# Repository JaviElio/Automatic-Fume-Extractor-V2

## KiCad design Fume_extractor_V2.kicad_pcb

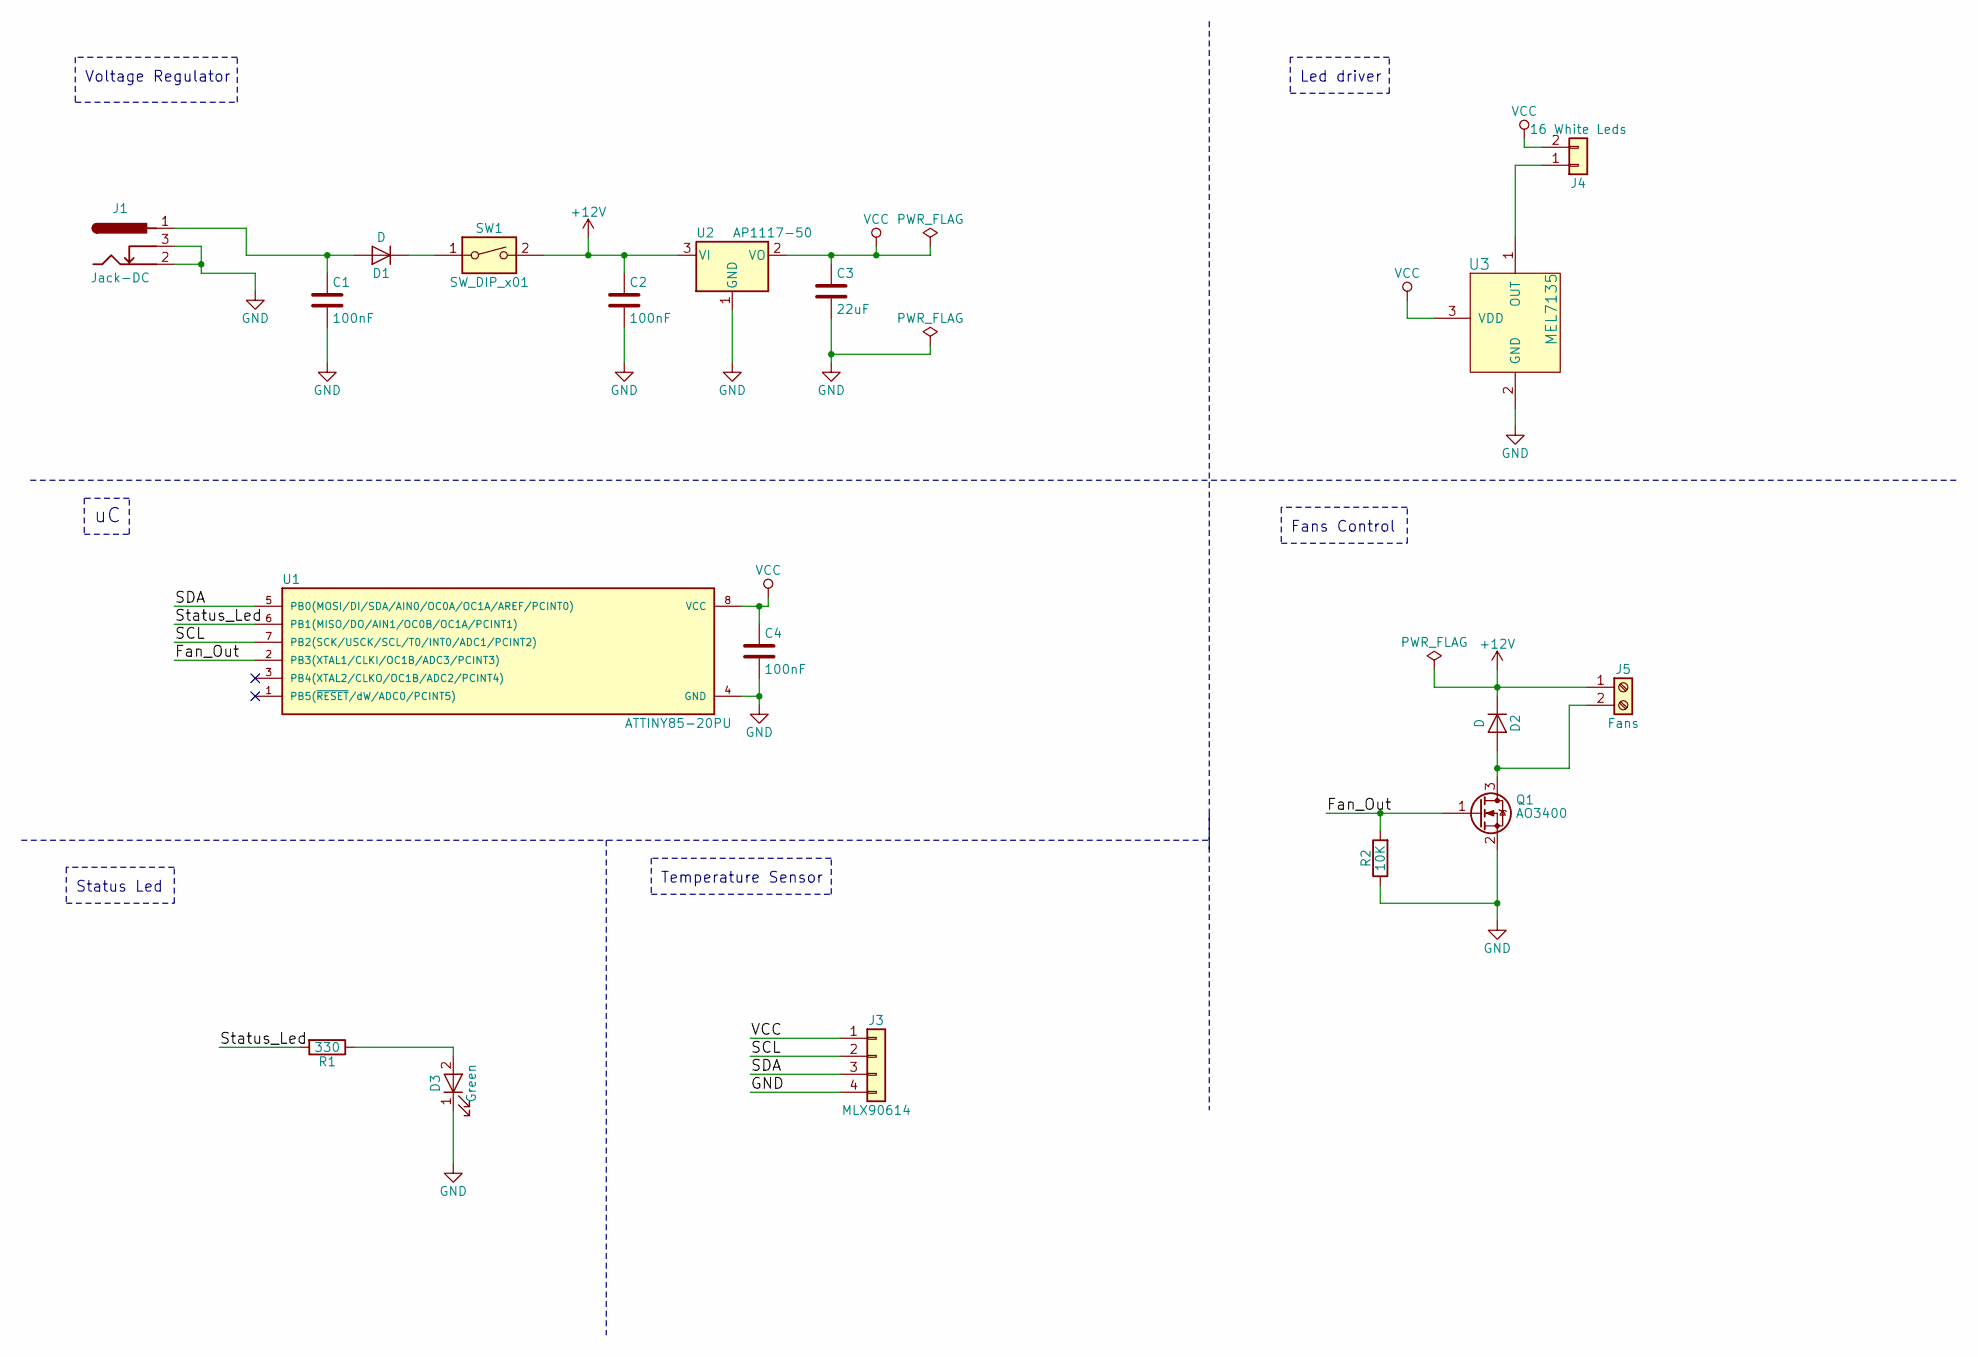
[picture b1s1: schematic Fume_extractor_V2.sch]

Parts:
C1, C2, C4: 100nF; C_0805_HandSoldering
C3: 22uF; CP_Tantalum_Case-A_EIA-3216-18_Hand
D1, D2: D; D_SMA_Handsoldering
D3: Green; LED_D3.0mm
J1: Jack-DC; BARREL_JACK
J3: MLX90614; Pin_Header_Straight_1x04_Pitch2.54mm
J4: 16 White Leds; JST_PH_B2B-PH-K_02x2.00mm_Straight
J5: Fans; TerminalBlock_2.54mm_2pol
Q1: AO3400; SOT-23
R1: 330; R_0805_HandSoldering
R2: 10K; R_0805_HandSoldering
SW1: SW_DIP_x01; JST_PH_B2B-PH-K_02x2.00mm_Straight
U1: ATTINY85-20PU; DIP-8_W7.62mm
U2: AP1117-50; SOT-223-3_TabPin2
U3: MEL7135; SOT-89-3_Handsoldering

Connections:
+12V: C2.1, D2.1 (K), J5.1, SW1.2, U2.3 (VI)
/Fan_Out: Q1.1 (G), R2.2, U1.2 (PB3(XTAL1/CLKI/OC1B/ADC3/PCINT3))
/SCL: J3.2, U1.7 (PB2(SCK/USCK/SCL/T0/INT0/ADC1/PCINT2))
/SDA: J3.3, U1.5 (PB0(MOSI/DI/SDA/AIN0/OC0A/OC1A/AREF/PCI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)
/Status_Led: R1.2, U1.6 (PB1(MISO/DO/AIN1/OC0B/OC1A/PCINT1))
GND: C1.2, C2.2, C3.2, C4.2, D3.1 (K), J1.2, J1.3, J3.4, Q1.2 (S), R2.1, U1.4 (GND), U2.1 (GND), U3.2 (GND)
unnamed: C1.1, D1.2 (A), J1.1
unnamed: D1.1 (K), SW1.1
unnamed: D2.2 (A), J5.2, Q1.3 (D)
unnamed: D3.2 (A), R1.1
unnamed: J4.1, U3.1 (OUT)
VCC: C3.1, C4.1, J3.1, J4.2, U1.8 (VCC), U2.2 (VO), U3.3 (VDD)

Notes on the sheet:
Voltage Regulator
Fans Control
Led driver
Status Led
Temperature Sensor

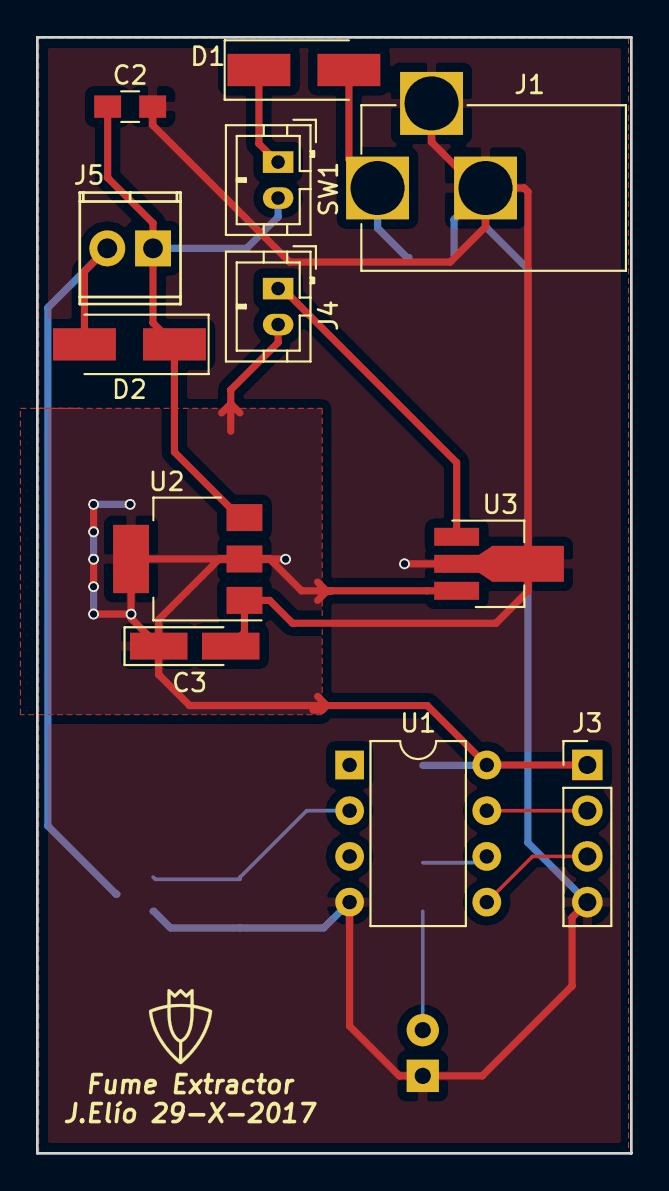
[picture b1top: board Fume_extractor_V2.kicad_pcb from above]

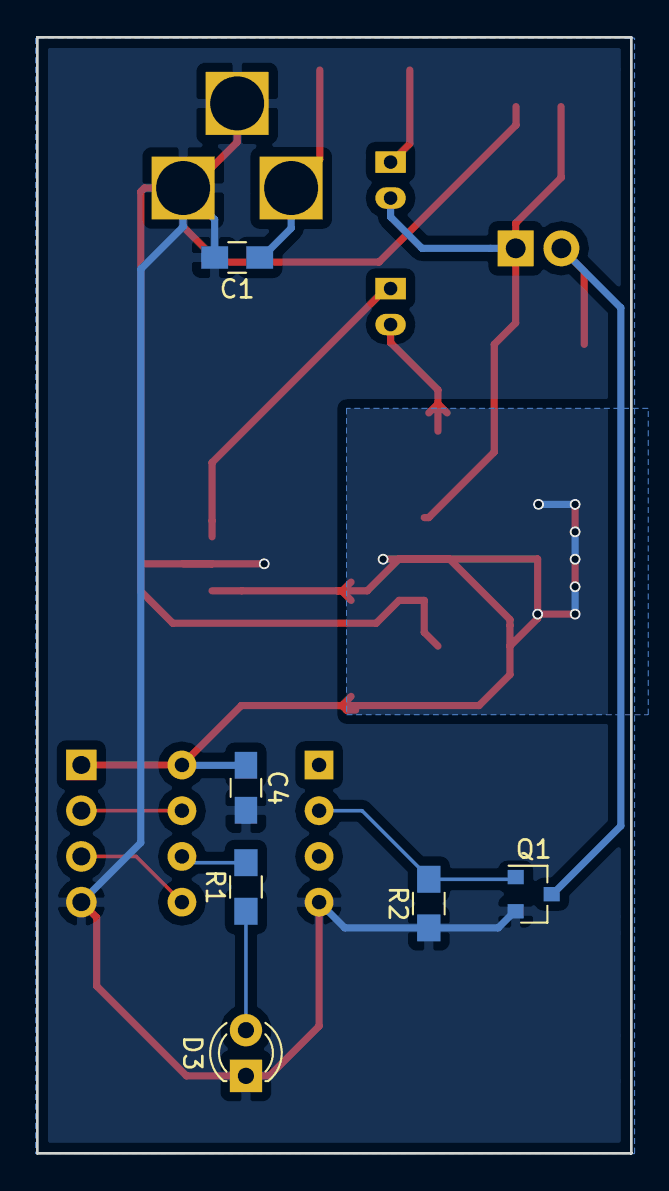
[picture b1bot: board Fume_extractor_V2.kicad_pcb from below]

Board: 2 copper layers, 33.0 x 62.0 mm, 18 parts (6 on the bottom side), 12 nets.

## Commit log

2017-12-08 First upload
